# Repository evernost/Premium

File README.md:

# Premium
Calculator for number factorisation.

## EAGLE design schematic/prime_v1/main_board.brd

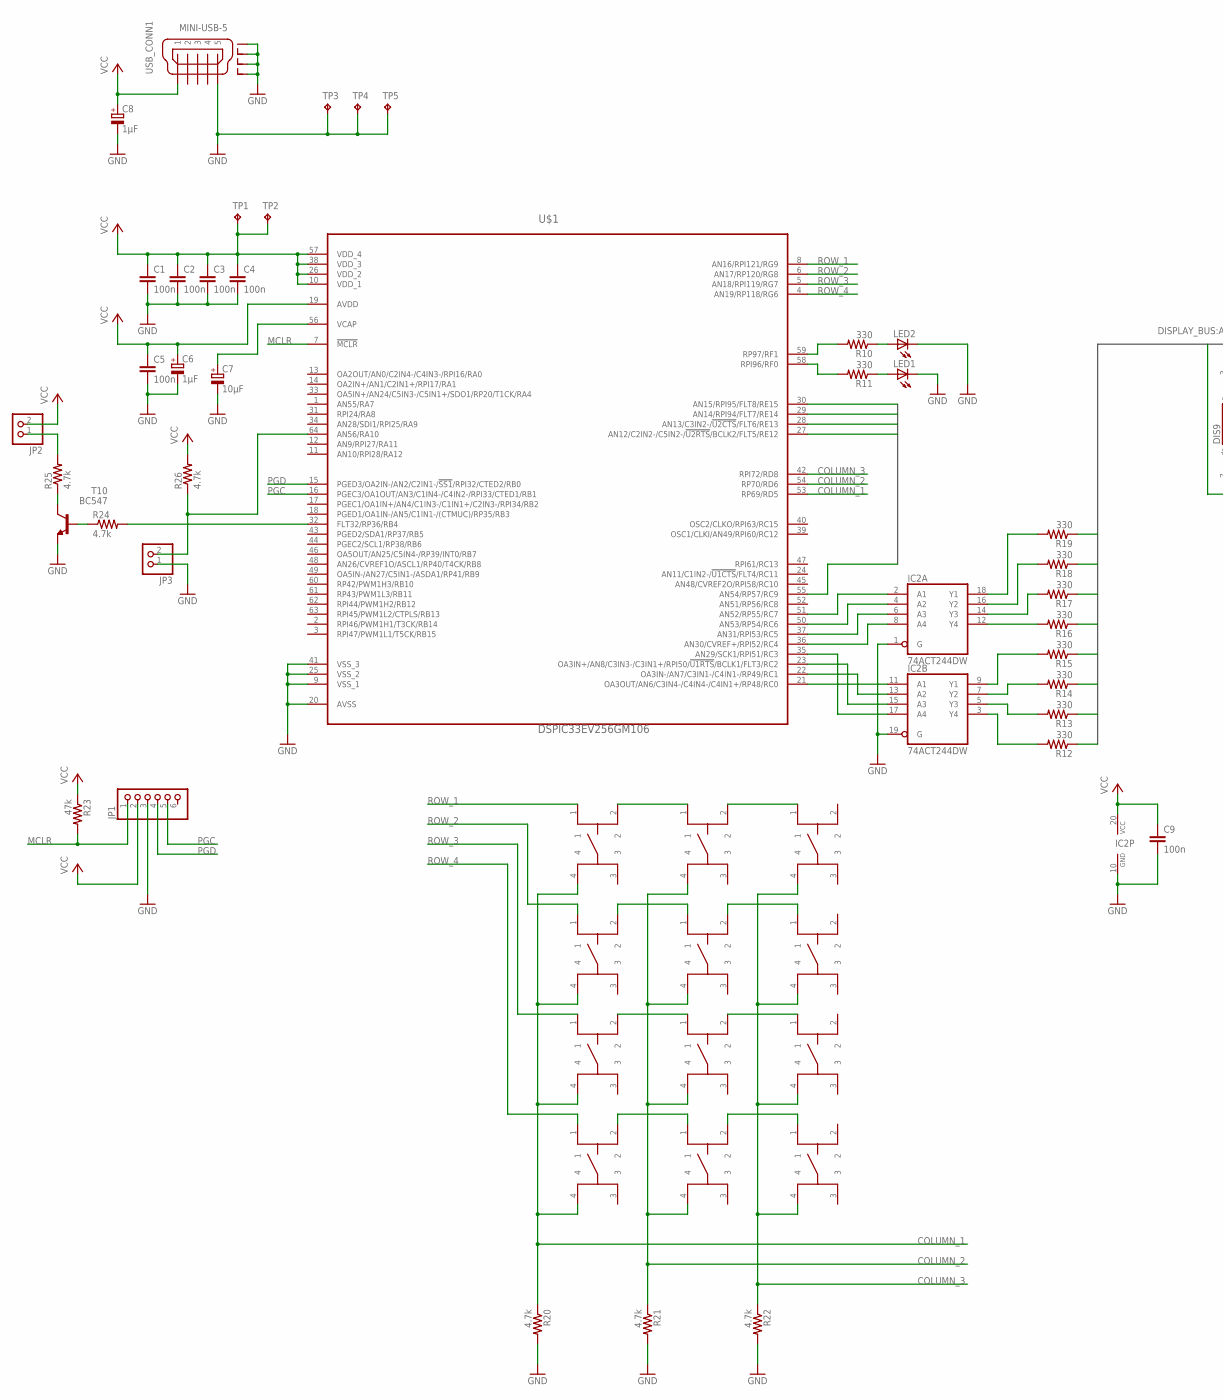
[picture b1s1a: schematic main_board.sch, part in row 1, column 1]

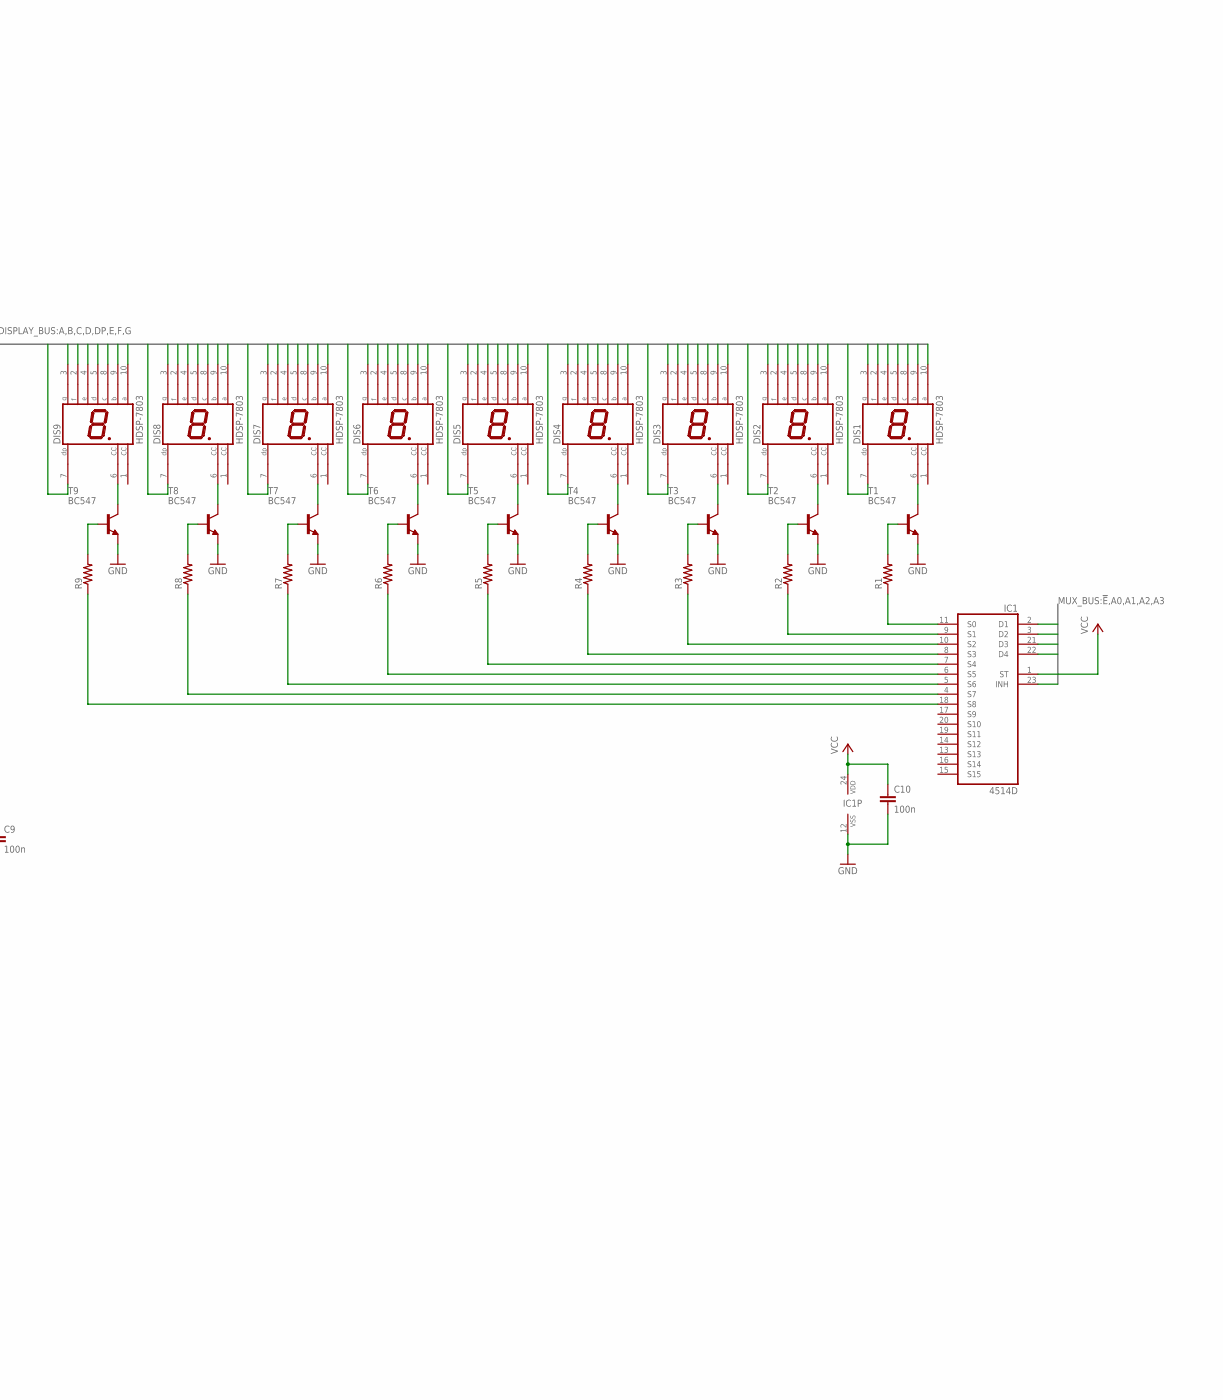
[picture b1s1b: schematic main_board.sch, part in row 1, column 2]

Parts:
B1, B2, B3, B4, B5, B6, B7, B8, B9, B10, B11, B12: KSC521G
C1, C2, C3, C4, C5, C9, C10: 100n; C050-025X075
C6, C8: 1µF; E2,5-7
C7: 10µF; E2,5-7
DIS1, DIS2, DIS3, DIS4, DIS5, DIS6, DIS7, DIS8, DIS9: HDSP-7803; HDSP-A
IC1: 4514D; SO24W
IC2: 74ACT244DW; SO20W
JP1: PINHD-1X6; 1X06
JP2, JP3: PINHD-1X2; 1X02
LED1, LED2: LED5MM
R1, R2, R3, R4, R5, R6, R7, R8, R9: R-US_0207/10; 0207/10
R10, R11, R12, R13, R14, R15, R16, R17, R18, R19: 330; 0207/10
R20, R21, R22, R24, R25, R26: 4.7k; 0207/10
R23: 47k; 0207/10
T1, T2, T3, T4, T5, T6, T7, T8, T9, T10: BC547; TO92
TP1, TP2, TP3, TP4, TP5: TPTP12SQ; TP12SQ
U$1: DSPIC33EV256GM106; TQFP64-10X10
USB_CONN1: MINI-USB-5; 56579-0579

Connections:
!E: IC1.23 (INH), U$1.55 (AN54/RP57/RC9)
A: DIS1.10 (A), DIS2.10 (A), DIS3.10 (A), DIS4.10 (A), DIS5.10 (A), DIS6.10 (A), DIS7.10 (A), DIS8.10 (A), DIS9.10 (A), R12.1
A0: IC1.2 (D1), U$1.27 (AN12/C2IN2-/C5IN2-/!U2RTS!/BCLK2/FLT5/R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)
A1: IC1.3 (D2), U$1.28 (AN13/C3IN2-/!U2CTS!/FLT6/RE13)
A2: IC1.21 (D3), U$1.29 (AN14/RPI94/FLT7/RE14)
A3: IC1.22 (D4), U$1.30 (AN15/RPI95/FLT8/RE15)
B: DIS1.9 (B), DIS2.9 (B), DIS3.9 (B), DIS4.9 (B), DIS5.9 (B), DIS6.9 (B), DIS7.9 (B), DIS8.9 (B), DIS9.9 (B), R13.1
C: DIS1.8 (C), DIS2.8 (C), DIS3.8 (C), DIS4.8 (C), DIS5.8 (C), DIS6.8 (C), DIS7.8 (C), DIS8.8 (C), DIS9.8 (C), R14.1
COLUMN_1: B1.4, B4.4, B7.4, B11.4, R20.1, U$1.53 (RP69/RD5)
COLUMN_2: B2.4, B5.4, B8.4, B10.4, R21.1, U$1.54 (RP70/RD6)
COLUMN_3: B3.4, B6.4, B9.4, B12.4, R22.1, U$1.42 (RPI72/RD8)
D: DIS1.5 (D), DIS2.5 (D), DIS3.5 (D), DIS4.5 (D), DIS5.5 (D), DIS6.5 (D), DIS7.5 (D), DIS8.5 (D), DIS9.5 (D), R15.1
DP: DIS1.7 (DP), DIS2.7 (DP), DIS3.7 (DP), DIS4.7 (DP), DIS5.7 (DP), DIS6.7 (DP), DIS7.7 (DP), DIS8.7 (DP), DIS9.7 (DP), R19.1
E: DIS1.4 (E), DIS2.4 (E), DIS3.4 (E), DIS4.4 (E), DIS5.4 (E), DIS6.4 (E), DIS7.4 (E), DIS8.4 (E), DIS9.4 (E), R16.1
F: DIS1.2 (F), DIS2.2 (F), DIS3.2 (F), DIS4.2 (F), DIS5.2 (F), DIS6.2 (F), DIS7.2 (F), DIS8.2 (F), DIS9.2 (F), R17.1
G: DIS1.3 (G), DIS2.3 (G), DIS3.3 (G), DIS4.3 (G), DIS5.3 (G), DIS6.3 (G), DIS7.3 (G), DIS8.3 (G), DIS9.3 (G), R18.1
GND: C1.2, C2.2, C3.2, C4.2, C5.2, C6.-, C7.-, C8.-, C9.2, C10.2, IC1.12 (VSS), IC2.1 (G), IC2.10 (GND), IC2.19 (G), JP1.3, JP3.1, LED1.K (C), LED2.K (C), R20.2, R21.2, R22.2, T1.1 (E), T2.1 (E), T3.1 (E), T4.1 (E), T5.1 (E), T6.1 (E), T7.1 (E), T8.1 (E), T9.1 (E), T10.1 (E), TP3.TP, TP4.TP, TP5.TP, U$1.9 (VSS_1), U$1.20 (AVSS), U$1.25 (VSS_2), U$1.41 (VSS_3), USB_CONN1.GND (5), USB_CONN1.SHIELD@1 (S1), USB_CONN1.SHIELD@2 (S2), USB_CONN1.SHIELD@3 (S3), USB_CONN1.SHIELD@4 (S4)
MCLR: JP1.1, R23.2, U$1.7 (!MCLR)
unnamed: DIS9.6 (CC), T9.3 (C)
unnamed: C7.+, U$1.56 (VCAP)
unnamed: DIS8.6 (CC), T8.3 (C)
unnamed: DIS7.6 (CC), T7.3 (C)
unnamed: DIS6.6 (CC), T6.3 (C)
unnamed: DIS5.6 (CC), T5.3 (C)
unnamed: DIS4.6 (CC), T4.3 (C)
unnamed: DIS3.6 (CC), T3.3 (C)
unnamed: DIS2.6 (CC), T2.3 (C)
unnamed: DIS1.6 (CC), T1.3 (C)
unnamed: R1.2, T1.2 (B)
unnamed: R2.2, T2.2 (B)
unnamed: R3.2, T3.2 (B)
unnamed: R4.2, T4.2 (B)
unnamed: R5.2, T5.2 (B)
unnamed: R6.2, T6.2 (B)
unnamed: R7.2, T7.2 (B)
unnamed: R8.2, T8.2 (B)
unnamed: R9.2, T9.2 (B)
unnamed: IC1.11 (S0), R1.1
unnamed: IC1.9 (S1), R2.1
unnamed: IC1.10 (S2), R3.1
unnamed: IC1.8 (S3), R4.1
unnamed: IC1.7 (S4), R5.1
unnamed: IC1.6 (S5), R6.1
unnamed: IC1.5 (S6), R7.1
unnamed: IC1.4 (S7), R8.1
unnamed: IC1.18 (S8), R9.1
unnamed: R10.2, U$1.59 (RP97/RF1)
unnamed: IC2.3 (Y4), R12.2
unnamed: LED1.A, R11.1
unnamed: R11.2, U$1.58 (RPI96/RF0)
unnamed: LED2.A, R10.1
unnamed: IC2.17 (A4), U$1.35 (AN29/SCK1/RPI51/RC3)
unnamed: IC2.15 (A3), U$1.23 (OA3IN+/AN8/C3IN3-/C3IN1+/RPI50/!U1RTS!/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)
unnamed: IC2.13 (A2), U$1.22 (OA3IN-/AN7/C3IN1-/C4IN1-/RP49/RC1)
unnamed: IC2.11 (A1), U$1.21 (OA3OUT/AN6/C3IN4-/C4IN4-/C4IN1+/RP48/RC0)
unnamed: IC2.8 (A4), U$1.36 (AN30/CVREF+/RPI52/RC4)
unnamed: IC2.6 (A3), U$1.37 (AN31/RPI53/RC5)
unnamed: IC2.4 (A2), U$1.50 (AN53/RP54/RC6)
unnamed: IC2.2 (A1), U$1.51 (AN52/RP55/RC7)
unnamed: IC2.5 (Y3), R13.2
unnamed: IC2.7 (Y2), R14.2
unnamed: IC2.9 (Y1), R15.2
unnamed: IC2.12 (Y4), R16.2
unnamed: IC2.14 (Y3), R17.2
unnamed: IC2.16 (Y2), R18.2
unnamed: IC2.18 (Y1), R19.2
unnamed: JP3.2, R26.1, U$1.64 (AN56/RA10)
unnamed: R24.1, T10.2 (B)
unnamed: R25.1, T10.3 (C)
unnamed: R24.2, U$1.32 (FLT32/RP36/RB4)
unnamed: JP2.1, R25.2
unnamed: B7.2, B8.1
unnamed: B1.2, B2.1
unnamed: B2.2, B3.1
unnamed: B4.2, B5.1
unnamed: B5.2, B6.1
unnamed: B8.2, B9.1
unnamed: B10.1, B11.2
unnamed: B10.2, B12.1
PGC: JP1.5, U$1.16 (PGEC3/OA1OUT/AN3/C1IN4-/C4IN2-/RPI33/CT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)
PGD: JP1.4, U$1.15 (PGED3/OA2IN-/AN2/C2IN1-/!SS1!/RPI32/CTE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)
ROW_1: B1.1, U$1.8 (AN16/RPI121/RG9)
ROW_2: B4.1, U$1.6 (AN17/RP120/RG8)
ROW_3: B7.1, U$1.5 (AN18/RPI119/RG7)
ROW_4: B11.1, U$1.4 (AN19/RP118/RG6)
VCC: C1.1, C2.1, C3.1, C4.1, C5.1, C6.+, C8.+, C9.1, C10.1, IC1.1 (ST), IC1.24 (VDD), IC2.20 (VCC), JP1.2, JP2.2, R23.1, R26.2, TP1.TP, TP2.TP, U$1.10 (VDD_1), U$1.19 (AVDD), U$1.26 (VDD_2), U$1.38 (VDD_3), U$1.57 (VDD_4), USB_CONN1.VBUS (1)

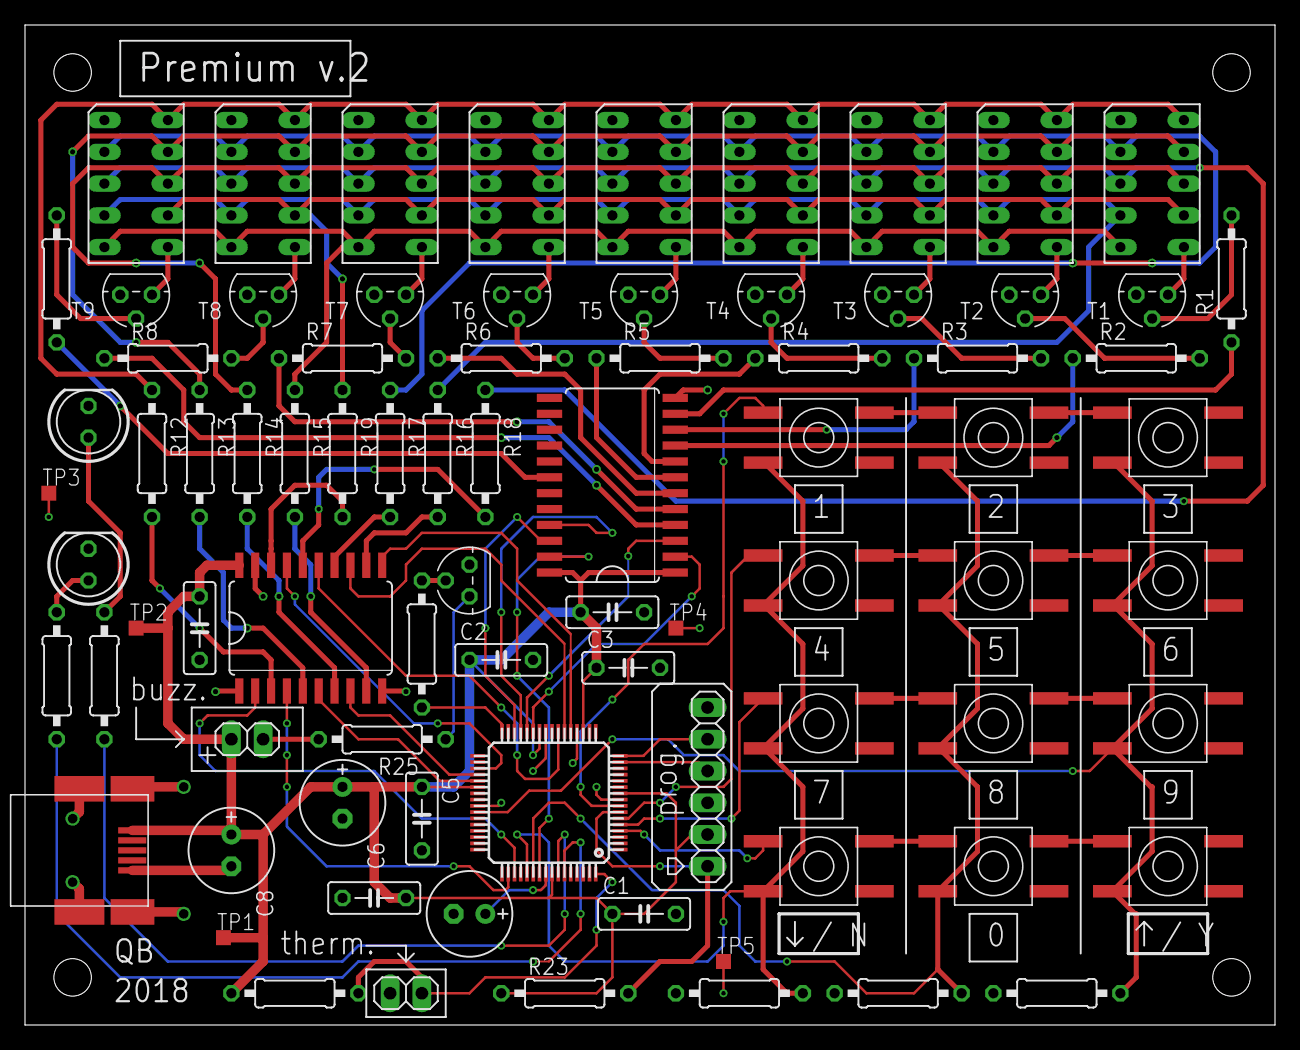
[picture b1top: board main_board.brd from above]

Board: 2 copper layers, 100.0 x 80.0 mm, 81 parts (0 on the bottom side), 86 nets.

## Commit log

2022-06-07 First upload of the current progress state.
